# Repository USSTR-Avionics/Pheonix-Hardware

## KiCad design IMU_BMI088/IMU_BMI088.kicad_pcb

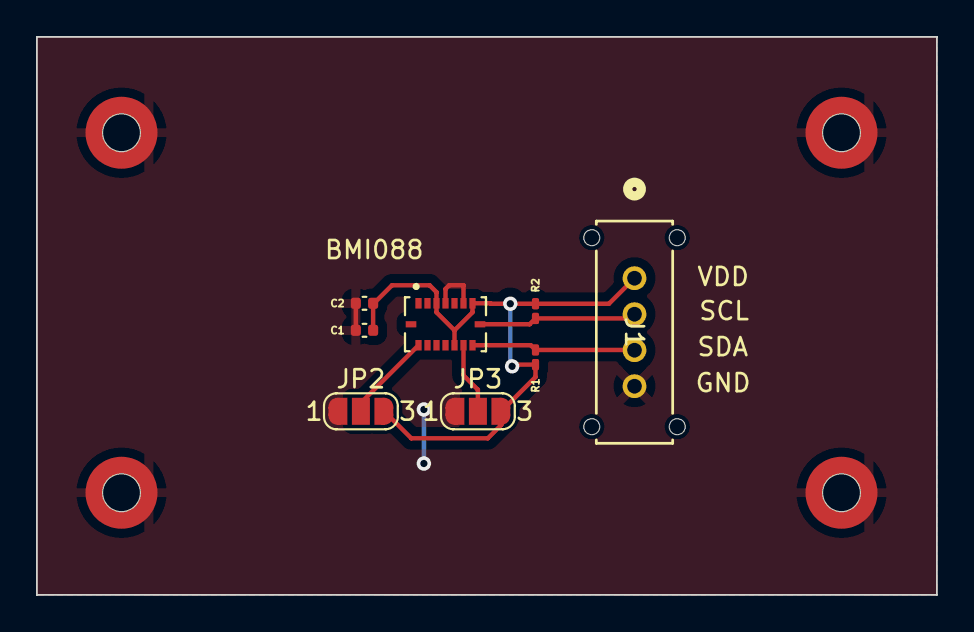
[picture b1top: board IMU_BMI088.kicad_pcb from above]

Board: 2 copper layers, 50.0 x 31.0 mm, 12 parts (0 on the bottom side), 6 nets.

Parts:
C1, C2: 100n; C_0402_1005Metric
H1, H2, H3, H4: MountingHole_Pad; Mounting_Wuerth_WA-SMSI-M1.6_H1mm_9774010633
IC1: BMI088; PQFN50P450X300X100-16N
J1: M80-8770422; CONN_M80-87704_HRW
JP2, JP3: SolderJumper_3_Open; SolderJumper-3_P1.3mm_Open_RoundedPad1.0x1.5mm_NumberLabels
R1, R2: 1.5k; R_0201_0603Metric_Pad0.64x0.40mm_HandSolder

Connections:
+3.3V: C1.1, C2.1, IC1.3 (VDD), IC1.7 (PS), IC1.11 (VDDIO), J1.1, JP2.3 (B), JP3.3 (B), R1.1, R2.1
/SCL: IC1.8 (SCL/SCK), J1.2, R2.2
/SDA: IC1.9 (SDA/SDI), J1.3, R1.2
GND: C1.2, C2.2, H1.1, H2.1, H3.1, H4.1, IC1.4 (GNDA), IC1.6 (GNDIO), J1.4, JP2.1 (A), JP3.1 (A)
unnamed: IC1.15 (SDO1), JP2.2 (C)
unnamed: IC1.10 (SDO2), JP3.2 (C)

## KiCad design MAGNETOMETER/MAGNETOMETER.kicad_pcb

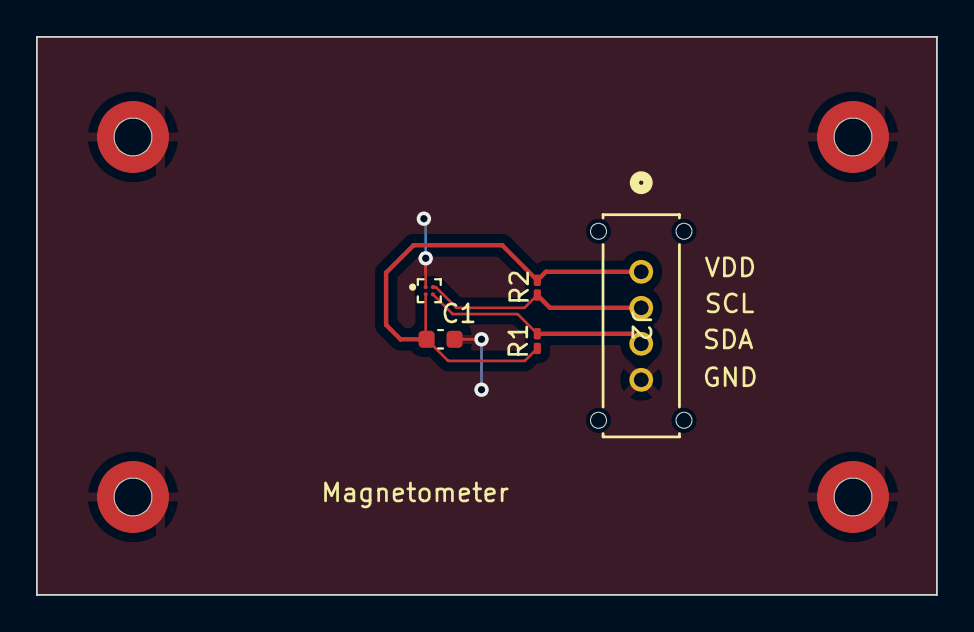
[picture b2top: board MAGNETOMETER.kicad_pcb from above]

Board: 2 copper layers, 50.0 x 31.0 mm, 9 parts (0 on the bottom side), 4 nets.

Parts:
C1: 2.2u; C_0603_1608Metric
H1, H2, H3, H4: MountingHole_Pad; Mounting_Wuerth_WA-SMSI-M1.6_H1mm_9774010633
IC1: MMC5603NJ; XDCR_MMC5603NJ
J2: M80-8770422; CONN_M80-87704_HRW
R1, R2: 1.5k; R_0201_0603Metric_Pad0.64x0.40mm_HandSolder

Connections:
+3.3V: C1.1, IC1.B1 (VDD), J2.1, R1.1, R2.1
/SCL: IC1.A2 (SCL), J2.2, R2.2
/SDA: IC1.B2 (SDA), J2.3, R1.2
GND: C1.2, H1.1, H2.1, H3.1, H4.1, IC1.A1 (VSA), J2.4

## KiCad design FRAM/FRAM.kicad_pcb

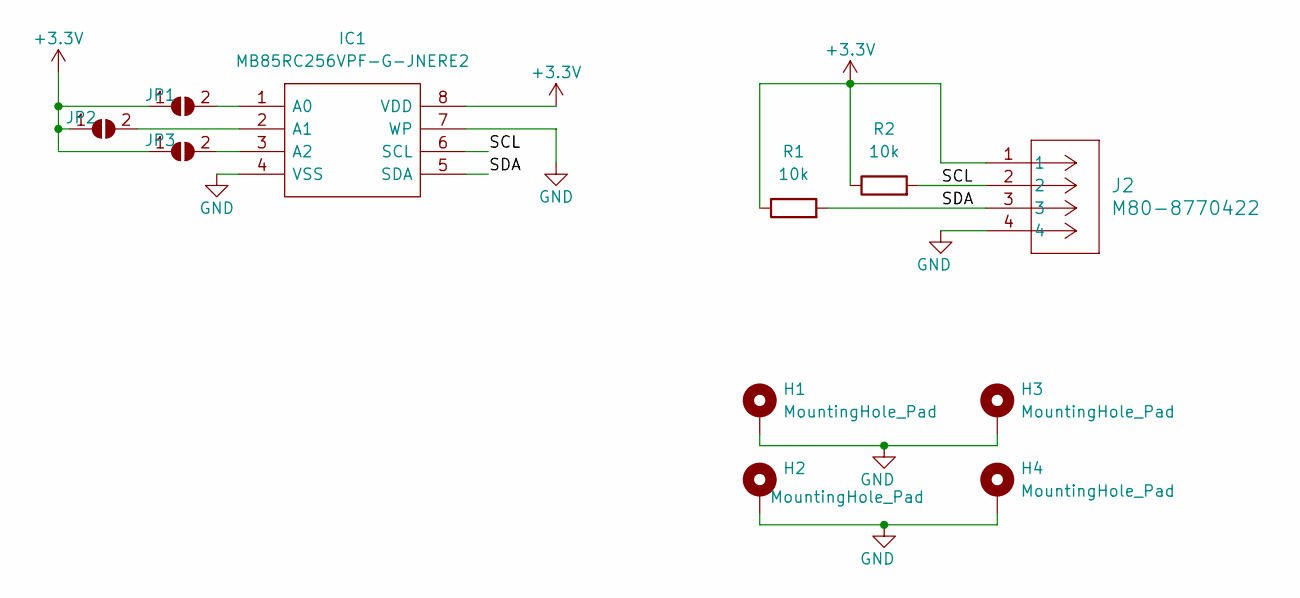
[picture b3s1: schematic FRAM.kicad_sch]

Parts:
H1, H2, H3, H4: MountingHole_Pad; Mounting_Wuerth_WA-SMSI-M1.6_H1mm_9774010633
IC1: MB85RC256VPF-G-JNERE2; FPT-8P-M08_FUJ; Manufacturer_Part_Number MB85RC256VPF-G-JNERE2; Mouser Part Number 249-MB85RC256VPJNRE2
J2: M80-8770422; CONN_M80-87704_HRW
JP1, JP2, JP3: SolderJumper_2_Open; SolderJumper-2_P1.3mm_Open_RoundedPad1.0x1.5mm
R1, R2: 10k; R_0201_0603Metric_Pad0.64x0.40mm_HandSolder

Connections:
+3.3V: J2.1, JP1.1 (A), JP2.1 (A), JP3.1 (A), R1.1, R2.1; also elsewhere on the board
/SCL: J2.2, R2.2; also elsewhere on the board
/SDA: J2.3, R1.2; also elsewhere on the board
GND: H1.1, H2.1, H3.1, H4.1, J2.4; also elsewhere on the board
unnamed 4: JP1.2 (B); also elsewhere on the board
unnamed 5: JP2.2 (B); also elsewhere on the board
unnamed 6: JP3.2 (B); also elsewhere on the board

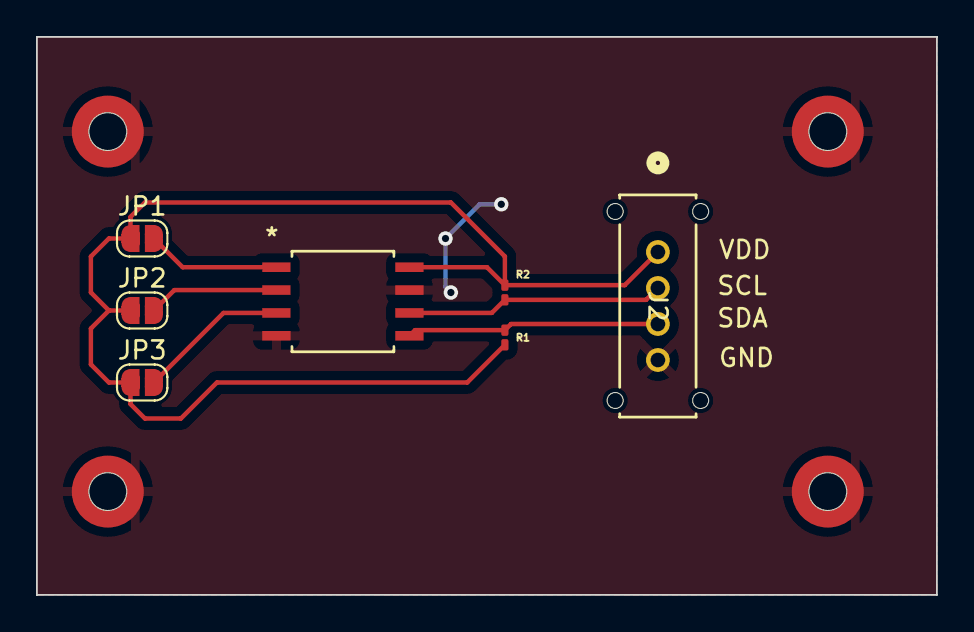
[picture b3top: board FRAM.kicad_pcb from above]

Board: 2 copper layers, 50.0 x 31.0 mm, 11 parts (0 on the bottom side), 7 nets.

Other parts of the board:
IC2: MB85RC256VPF-G-JNERE2; FPT-8P-M08_FUJ

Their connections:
+3.3V: IC2.8 (VDD); also elsewhere on the board
/SCL: IC2.6 (SCL); also elsewhere on the board
/SDA: IC2.5 (SDA); also elsewhere on the board
GND: IC2.4 (VSS), IC2.7 (WP); also elsewhere on the board
unnamed 4: IC2.1 (A0); also elsewhere on the board
unnamed 5: IC2.2 (A1); also elsewhere on the board
unnamed 6: IC2.3 (A2); also elsewhere on the board

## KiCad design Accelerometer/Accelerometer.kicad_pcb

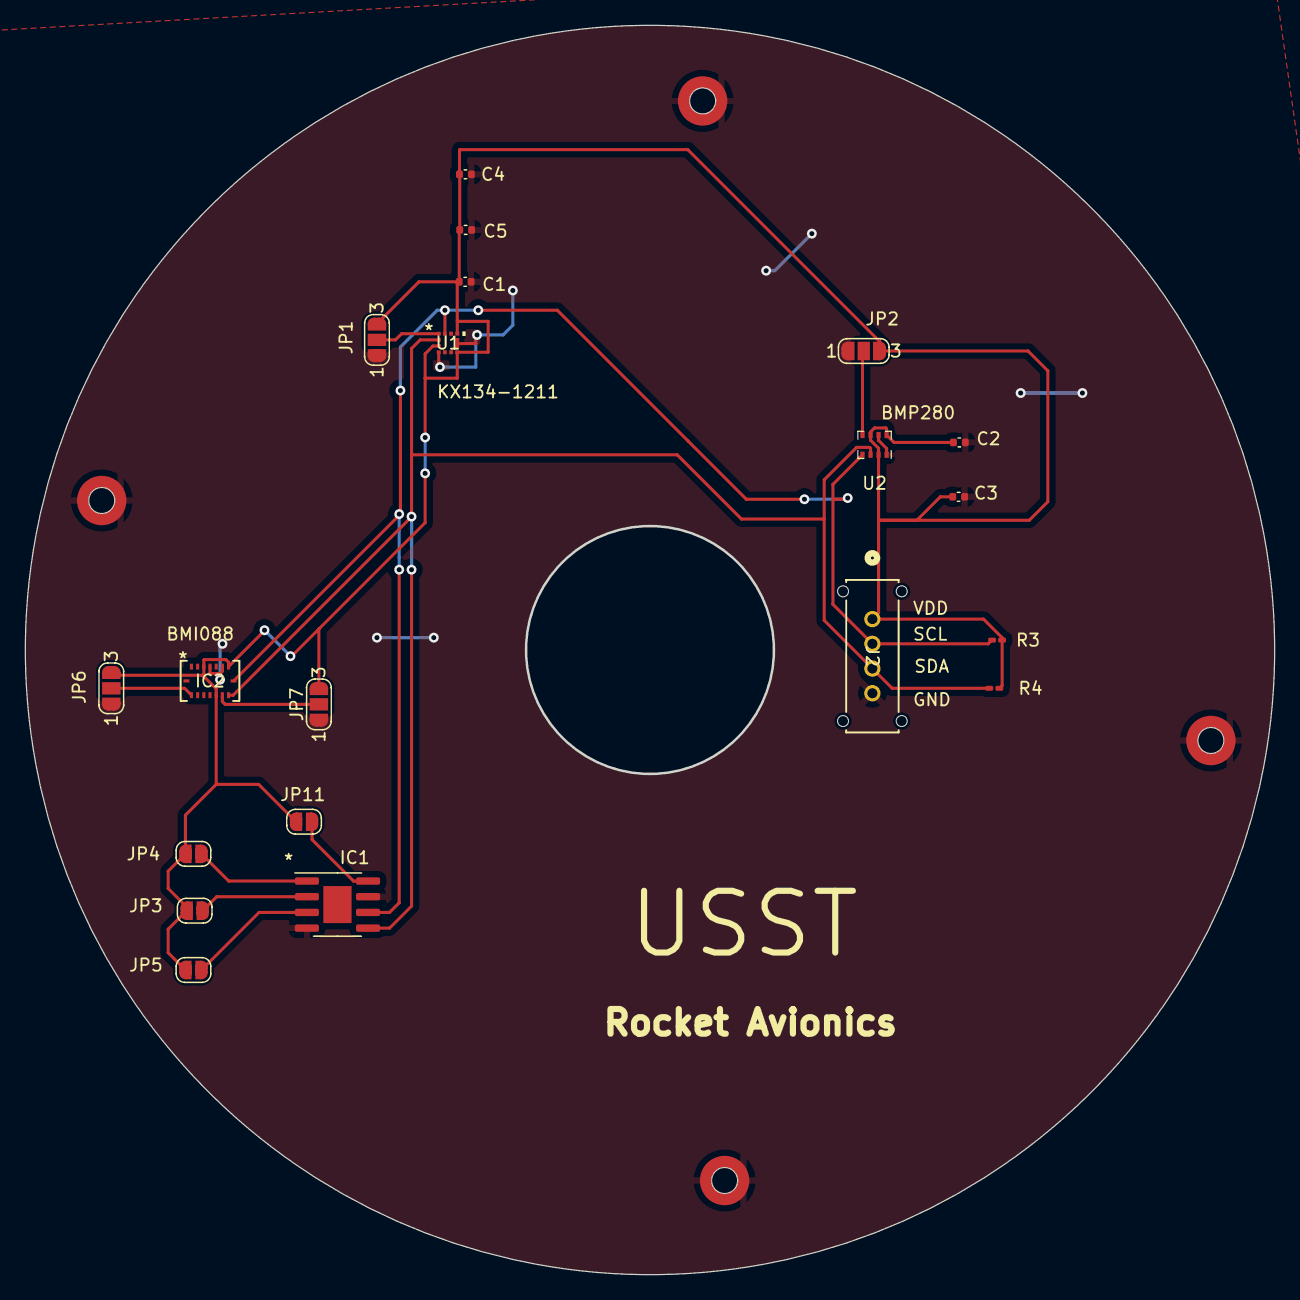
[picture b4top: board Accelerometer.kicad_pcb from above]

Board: 2 copper layers, 101.1 x 101.1 mm, 24 parts (0 on the bottom side), 11 nets.

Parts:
C1: 0.1u; C_0402_1005Metric
C2, C3: 100nF; C_0402_1005Metric
C4, C5: 100n; C_0402_1005Metric
H1, H2, H3, H4: MountingHole_Pad; Mounting_Wuerth_WA-SMSI-M1.6_H1mm_9774010633
IC1: FRAM; SOIC-8-1EP_3.9x4.9mm_P1.27mm_EP2.29x3mm
IC2: BMI088; QFN_BMI085_BOS
J2: M80-8770422; CONN_M80-87704_HRW
JP1, JP2, JP6, JP7: SolderJumper_3_Open; SolderJumper-3_P1.3mm_Open_RoundedPad1.0x1.5mm_NumberLabels
JP3, JP4, JP5, JP11: SolderJumper_2_Open; SolderJumper-2_P1.3mm_Open_RoundedPad1.0x1.5mm
R3, R4: 1.5k; R_0201_0603Metric_Pad0.64x0.40mm_HandSolder
U1: KX134-1211; LGA12_2X2X0P9_ROM
U2: BMP280; Bosch_LGA-8_2x2.5mm_P0.65mm_ClockwisePinNumbering

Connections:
+3.3V: C1.1, C2.1, C3.1, C4.1, C5.1, IC1.8 (VDD), IC2.3 (VDD), IC2.7 (PS), IC2.11 (VDDIO), J2.1, JP1.3 (B), JP2.3 (B), JP3.1 (A), JP4.1 (A), JP5.1 (A), JP6.3 (B), JP7.3 (B), JP11.2 (B), R3.1, R4.1, U1.3 (IO_VDD), U1.7 (VDD), U1.10 (nCS), U2.2 (CSB), U2.6 (VDDIO), U2.8 (VDD)
/SCL: IC1.6 (SCL), IC2.8 (SCL/SCK), J2.2, R3.2, U1.12 (SCLK/SCL), U2.4 (SCK)
/SDA: IC1.5 (SDA), IC2.9 (SDA/SDI), J2.3, R4.2, U1.2 (SDI/SDA), U2.3 (SDI)
GND: C1.2, C2.2, C3.2, C4.2, C5.2, H1.1, H2.1, H3.1, H4.1, IC1.4 (VSS), IC1.7 (WP), IC2.4 (GNDA), IC2.6 (GNDIO), J2.4, JP1.1 (A), JP2.1 (A), JP6.1 (A), JP7.1 (A), U1.4 (TRIG), U1.8 (GND), U1.9 (GND), U2.1 (GND), U2.7 (GND)
unnamed: IC1.1 (A0), JP4.2 (B)
unnamed: IC1.2 (A1), JP3.2 (B)
unnamed: IC1.3 (A2), JP5.2 (B)
unnamed: IC2.15 (SDO1), JP6.2 (C)
unnamed: IC2.10 (SDO2), JP7.2 (C)
unnamed: JP1.2 (C), U1.1 (SDO/ADDR)
unnamed: JP2.2 (C), U2.5 (SDO)

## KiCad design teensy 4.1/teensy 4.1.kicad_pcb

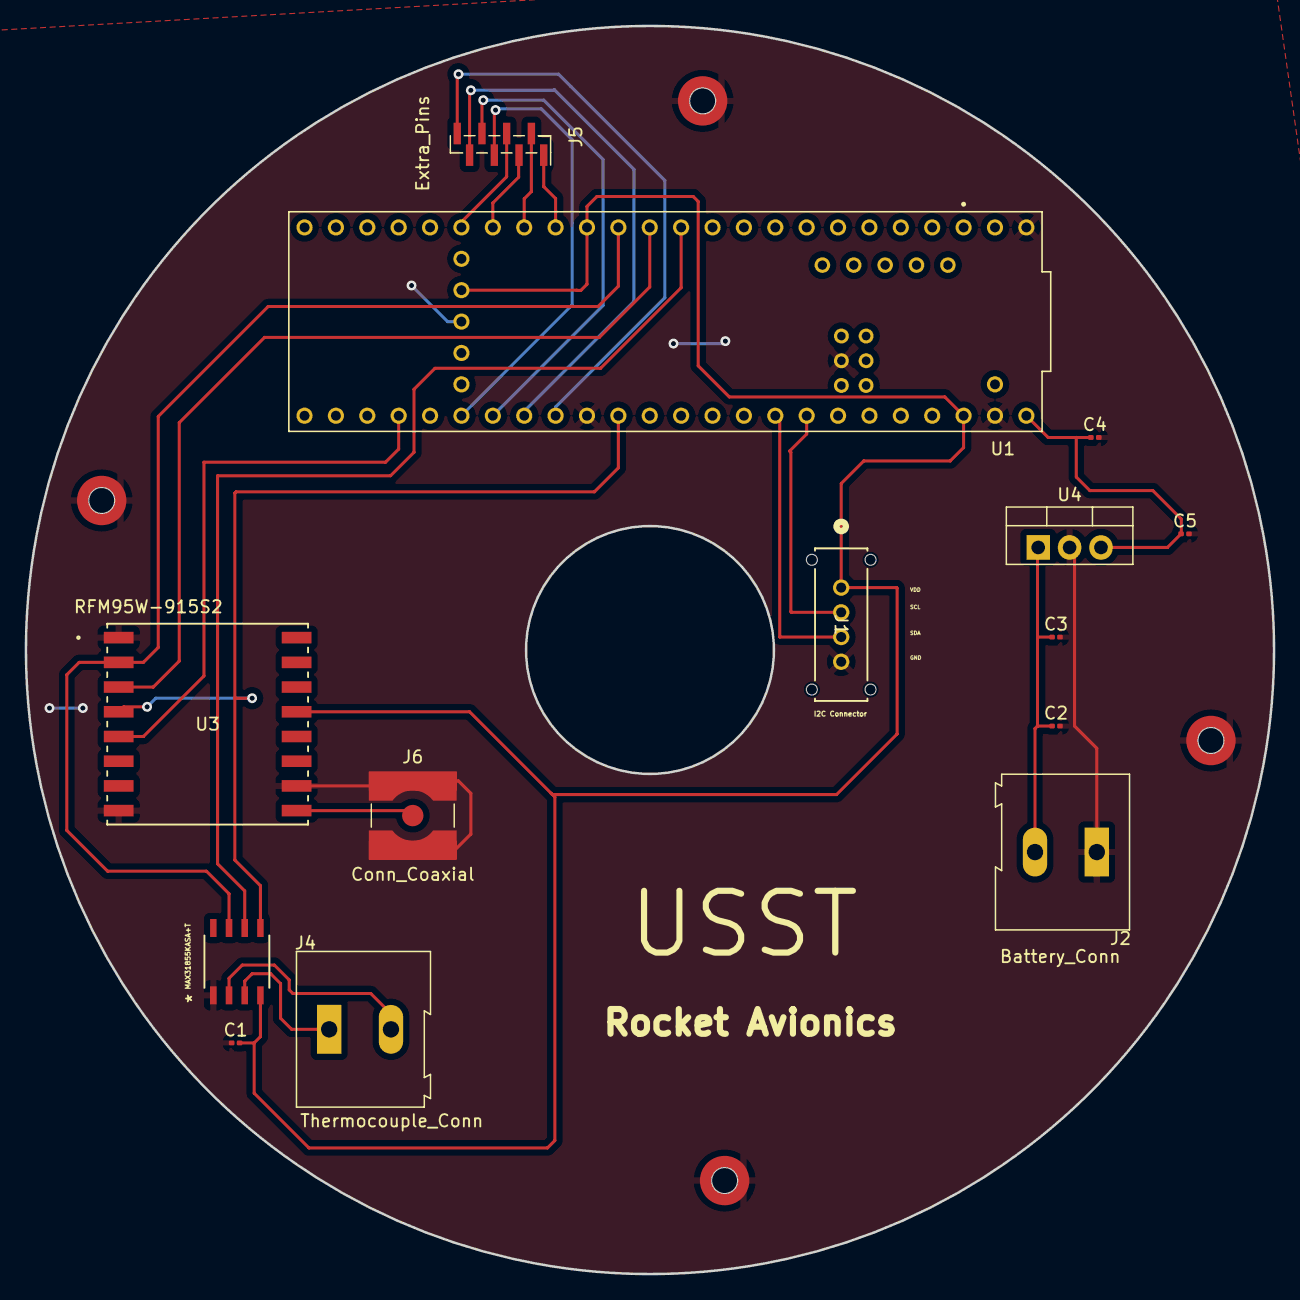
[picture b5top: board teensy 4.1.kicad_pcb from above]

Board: 2 copper layers, 101.0 x 101.0 mm, 18 parts (0 on the bottom side), 22 nets.

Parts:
C1: 100nF; C_0201_0603Metric
C2: 470uF; C_0201_0603Metric
C3, C4: 0.1uF; C_0201_0603Metric
C5: 220uF; C_0201_0603Metric
H1, H2, H3, H4: MountingHole_Pad; Mounting_Wuerth_WA-SMSI-M1.6_H1mm_9774010633
J1: M80-8770422; CONN_M80-87704_HRW
J2: Battery_Conn; TerminalBlock_Altech_AK300-2_P5.00mm
J4: Thermocouple_Conn; TerminalBlock_Altech_AK300-2_P5.00mm
J5: Extra_Pins; PinHeader_1x08_P1.00mm_Vertical_SMD_Pin1Right
J6: Conn_Coaxial; SMA_Amphenol_132134-10_Vertical
U1: DEV-16771; MODULE_DEV-16771
U3: RFM95W-915S2; IC16_RFM95W-915S2_RFS-M
U4: LM7805_TO220; TO-220-3_Vertical
U5: MAX31855KASA+T; 21-0041B_8_MXM

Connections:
+3.3V: C1.2, J1.1, U1.3.3V_1 (3.3V), U1.3.3V_2 (3.3V), U1.3.3V_3 (3.3V), U3.13 (3.3V), U5.4 (VCC)
+5V: C4.1, C5.1, U1.VIN, U4.3 (VO)
/CS1: U1.10 (CS1), U5.6 (*CS)
/CS2: U1.36 (CS2), U3.5 (NSS)
/I2C1_SCL: J1.2, U1.19 (A5)
/I2C1_SDA: J1.3, U1.18 (A4)
/MISO: U1.12 (MISO), U3.2 (MISO), U5.7 (SO)
/MOSI: U1.11 (MOSI), U3.3 (MOSI)
/SPI_CLK: U1.13 (SCK), U3.4 (SCK), U5.5 (SCK)
GND: C1.1, C2.2, C3.2, C4.2, C5.2, H1.1, H2.1, H3.1, H4.1, J1.4, J2.1, J6.2 (Ext), U1.GND1 (GND), U1.GND2 (GND), U1.GND3 (GND), U1.GND4 (GND), U1.GND5 (GND), U3.1 (GND), U3.8 (GND), U3.10 (GND), U4.2 (GND), U5.1 (GND)
unnamed: C2.1, C3.1, J2.2, U4.1 (VI)
unnamed: J4.1, U5.3 (T+)
unnamed: J4.2, U5.2 (T-)
unnamed: J5.1, U1.24 (A10)
unnamed: J5.2, U1.25 (A11)
unnamed: J5.3, U1.26 (A12)
unnamed: J5.4, U1.27 (A13)
unnamed: J5.5, U1.38 (A14)
unnamed: J5.6, U1.39 (A15)
unnamed: J5.7, U1.40 (A16)
unnamed: J5.8, U1.41 (A17)
unnamed: J6.1 (In), U3.9 (ANT)

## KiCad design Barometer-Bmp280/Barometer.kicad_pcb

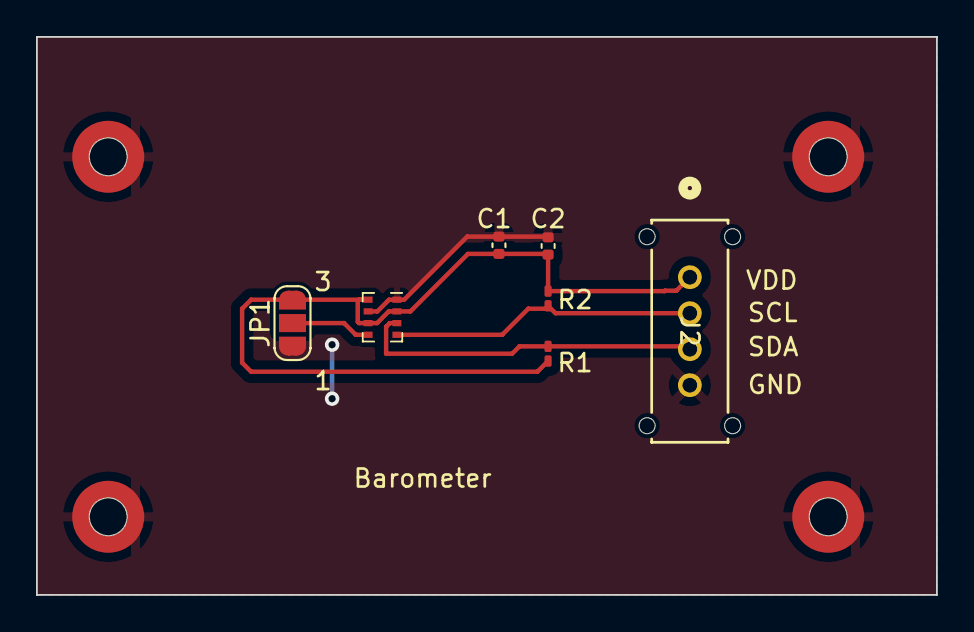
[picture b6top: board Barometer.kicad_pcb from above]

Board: 2 copper layers, 50.0 x 31.0 mm, 11 parts (0 on the bottom side), 5 nets.

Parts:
C1, C2: 100nF; C_0402_1005Metric
H1, H2, H3, H4: MountingHole_Pad; Mounting_Wuerth_WA-SMSI-M1.6_H1mm_9774010633
J2: M80-8770422; CONN_M80-87704_HRW
JP1: SolderJumper_3_Open; SolderJumper-3_P1.3mm_Open_RoundedPad1.0x1.5mm_NumberLabels
R1, R2: 1.5k; R_0201_0603Metric_Pad0.64x0.40mm_HandSolder
U1: BMP280; Bosch_LGA-8_2x2.5mm_P0.65mm_ClockwisePinNumbering

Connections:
+3.3V: C1.1, C2.1, J2.1, JP1.3 (B), R1.1, R2.1, U1.2 (CSB), U1.6 (VDDIO), U1.8 (VDD)
/SCL: J2.2, R2.2, U1.4 (SCK)
/SDA: J2.3, R1.2, U1.3 (SDI)
GND: C1.2, C2.2, H1.1, H2.1, H3.1, H4.1, J2.4, JP1.1 (A), U1.1 (GND), U1.7 (GND)
unnamed: JP1.2 (C), U1.5 (SDO)

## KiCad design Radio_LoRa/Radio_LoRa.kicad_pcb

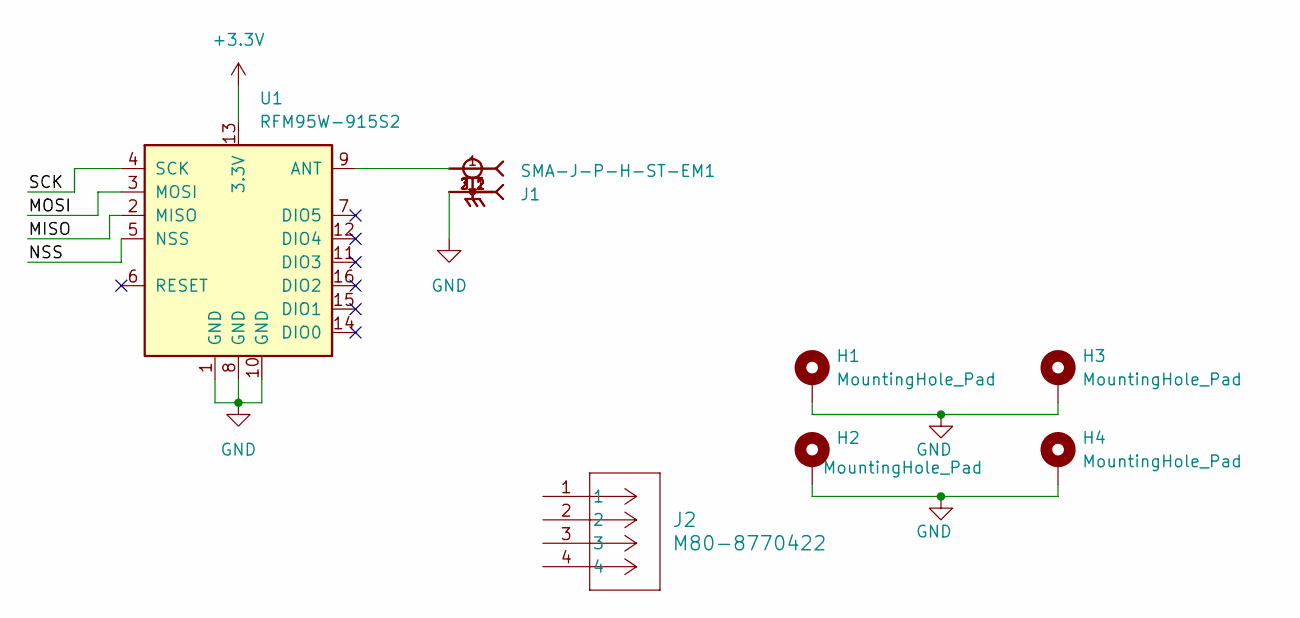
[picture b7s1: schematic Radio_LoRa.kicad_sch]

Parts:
H1, H2, H3, H4: MountingHole_Pad; Mounting_Wuerth_WA-SMSI-M1.6_H1mm_9774010633
J1: SMA-J-P-H-ST-EM1; SAMTEC_SMA-J-P-H-ST-EM1; PARTREV G
J2: M80-8770422; CONN_M80-87704_HRW
U1: RFM95W-915S2; XCVR_RFM95W-915S2

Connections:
+3.3V: U1.13 (3.3V)
/MISO: U1.2 (MISO)
/MOSI: U1.3 (MOSI)
/NSS: U1.5 (NSS)
/SCK: U1.4 (SCK)
GND: H1.1, H2.1, H3.1, H4.1, J1.2_1, J1.2_2, J1.3_1, J1.3_2, U1.1 (GND), U1.8 (GND), U1.10 (GND)
unnamed: J1.1, U1.9 (ANT)

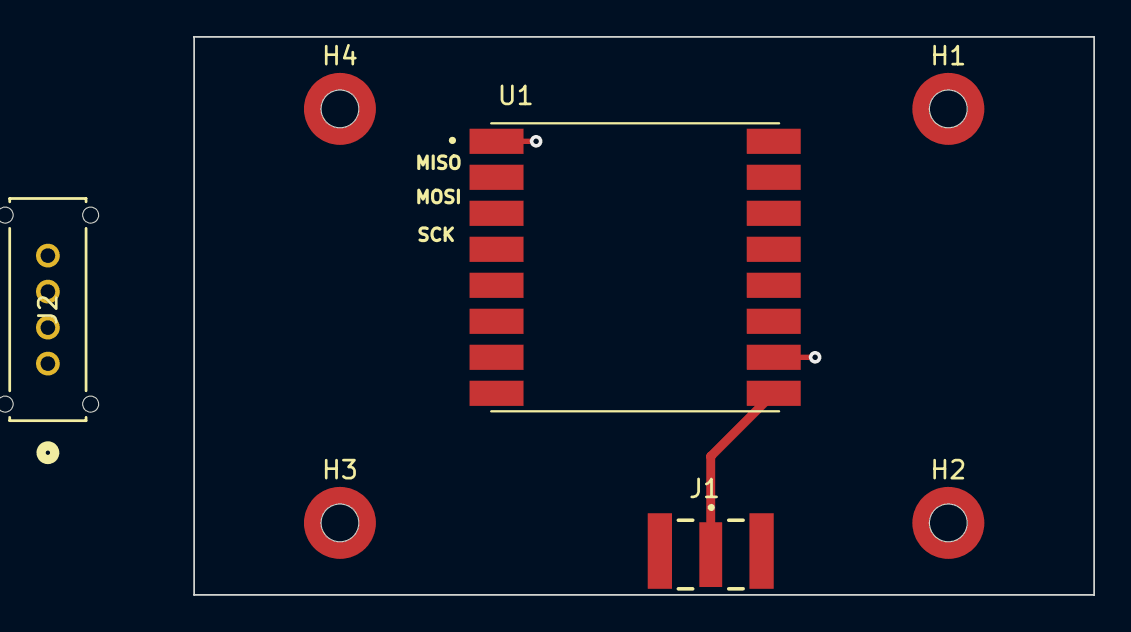
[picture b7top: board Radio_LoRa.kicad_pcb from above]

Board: 2 copper layers, 50.0 x 31.0 mm, 7 parts (0 on the bottom side), 2 nets.

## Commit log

2024-02-03 Initial commit. Adding files to git
2024-03-02 Route sensors, IMU and radio board
2024-03-16 Done with most of the boards
2024-05-11 No major design change. A few annotations changed
2024-06-13 Fixed Accel, Barometer, FRAM, Inertia unit, and Magnetometer
2024-06-29 Started fixing layouts
2024-09-14 LC24 PCBs
